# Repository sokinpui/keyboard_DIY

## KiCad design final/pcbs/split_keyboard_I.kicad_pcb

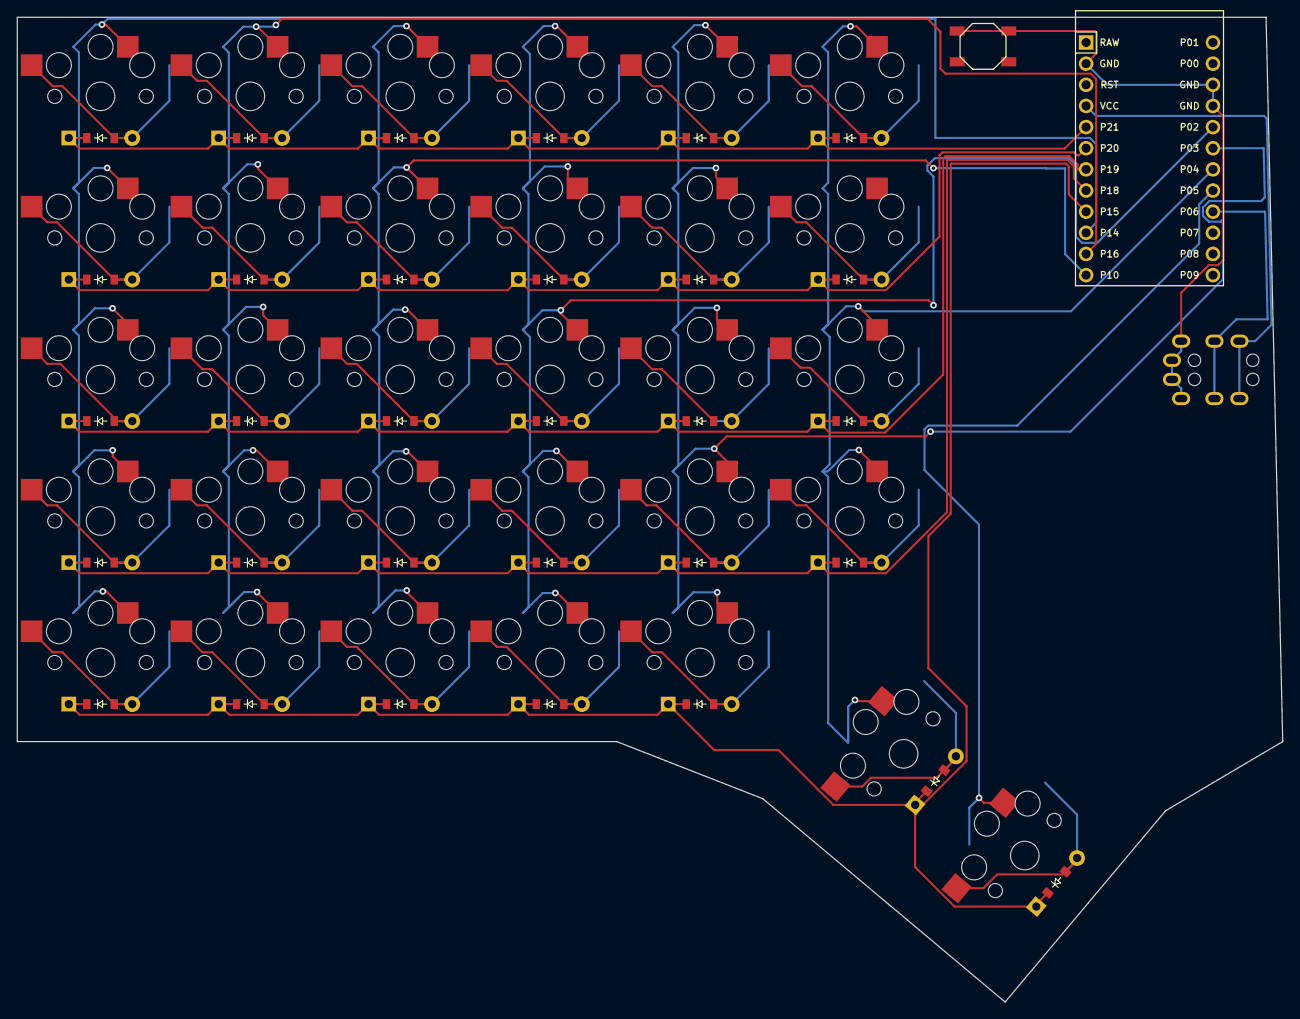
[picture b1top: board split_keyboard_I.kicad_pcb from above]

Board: 2 copper layers, 152.0 x 118.3 mm, 65 parts (0 on the bottom side), 47 nets.

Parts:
B1: SW_TACT_ALPS_SKQGABE010
D1, D2, D3, D4, D5, D6, D7, D8, D9, D10, D11, D12, D13, D14, D15, D16, D17, D18, D19, D20, D21, D22, D23, D24, D25, D26, D27, D28, D29, D30, D31: ComboDiode
MCU1: ProMicro
S1, S2, S3, S4, S5, S6, S7, S8, S9, S10, S11, S12, S13, S14, S15, S16, S17, S18, S19, S20, S21, S22, S23, S24, S25, S26, S27, S28, S29, S30, S31: PG1350
TRRS1: TRRS-PJ-320A-dual

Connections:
GND: B1.1, MCU1.2, MCU1.15, MCU1.16, TRRS1.1, TRRS1.2
P2: MCU1.17, S16.1, S17.1, S18.1, S19.1, S20.1
P3: MCU1.18, S21.1, S22.1, S23.1, S24.1, S25.1
P4: MCU1.19, S26.1, S27.1, S28.1, S29.1, S30.1
P5: MCU1.20, S31.1
P6: MCU1.21, TRRS1.3
P10: MCU1.12, S11.1, S12.1, S13.1, S14.1, S15.1
P14: MCU1.10, S1.1, S2.1, S3.1, S4.1, S5.1
P15: D1.1, D6.1, D11.1, D16.1, D21.1, D30.1, D31.1, MCU1.9
P16: MCU1.11, S6.1, S7.1, S8.1, S9.1, S10.1
P18: D2.1, D7.1, D12.1, D17.1, D22.1, D26.1, MCU1.8
P19: D3.1, D8.1, D13.1, D18.1, D23.1, D27.1, MCU1.7
P20: D4.1, D9.1, D14.1, D19.1, D24.1, D28.1, MCU1.6
P21: D5.1, D10.1, D15.1, D20.1, D25.1, D29.1, MCU1.5
RST: B1.2, MCU1.3
VCC: MCU1.4, TRRS1.4
index_bottom: D21.2, S21.2
index_number: D25.2, S25.2
index_row1: D24.2, S24.2
index_row2: D23.2, S23.2
index_row3: D22.2, S22.2
inner_number: D29.2, S29.2
inner_row1: D28.2, S28.2
inner_row2: D27.2, S27.2
inner_row3: D26.2, S26.2
layer_cluster: D31.2, S31.2
middle_bottom: D16.2, S16.2
middle_number: D20.2, S20.2
middle_row1: D19.2, S19.2
middle_row2: D18.2, S18.2
middle_row3: D17.2, S17.2
outer_bottom: D1.2, S1.2
outer_number: D5.2, S5.2
outer_row1: D4.2, S4.2
outer_row2: D3.2, S3.2
outer_row3: D2.2, S2.2
pinky_bottom: D6.2, S6.2
pinky_number: D10.2, S10.2
pinky_row1: D9.2, S9.2
pinky_row2: D8.2, S8.2
pinky_row3: D7.2, S7.2
ring_bottom: D11.2, S11.2
ring_number: D15.2, S15.2
ring_row1: D14.2, S14.2
ring_row2: D13.2, S13.2
ring_row3: D12.2, S12.2
space_cluster: D30.2, S30.2

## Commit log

2023-08-27 named pcb
